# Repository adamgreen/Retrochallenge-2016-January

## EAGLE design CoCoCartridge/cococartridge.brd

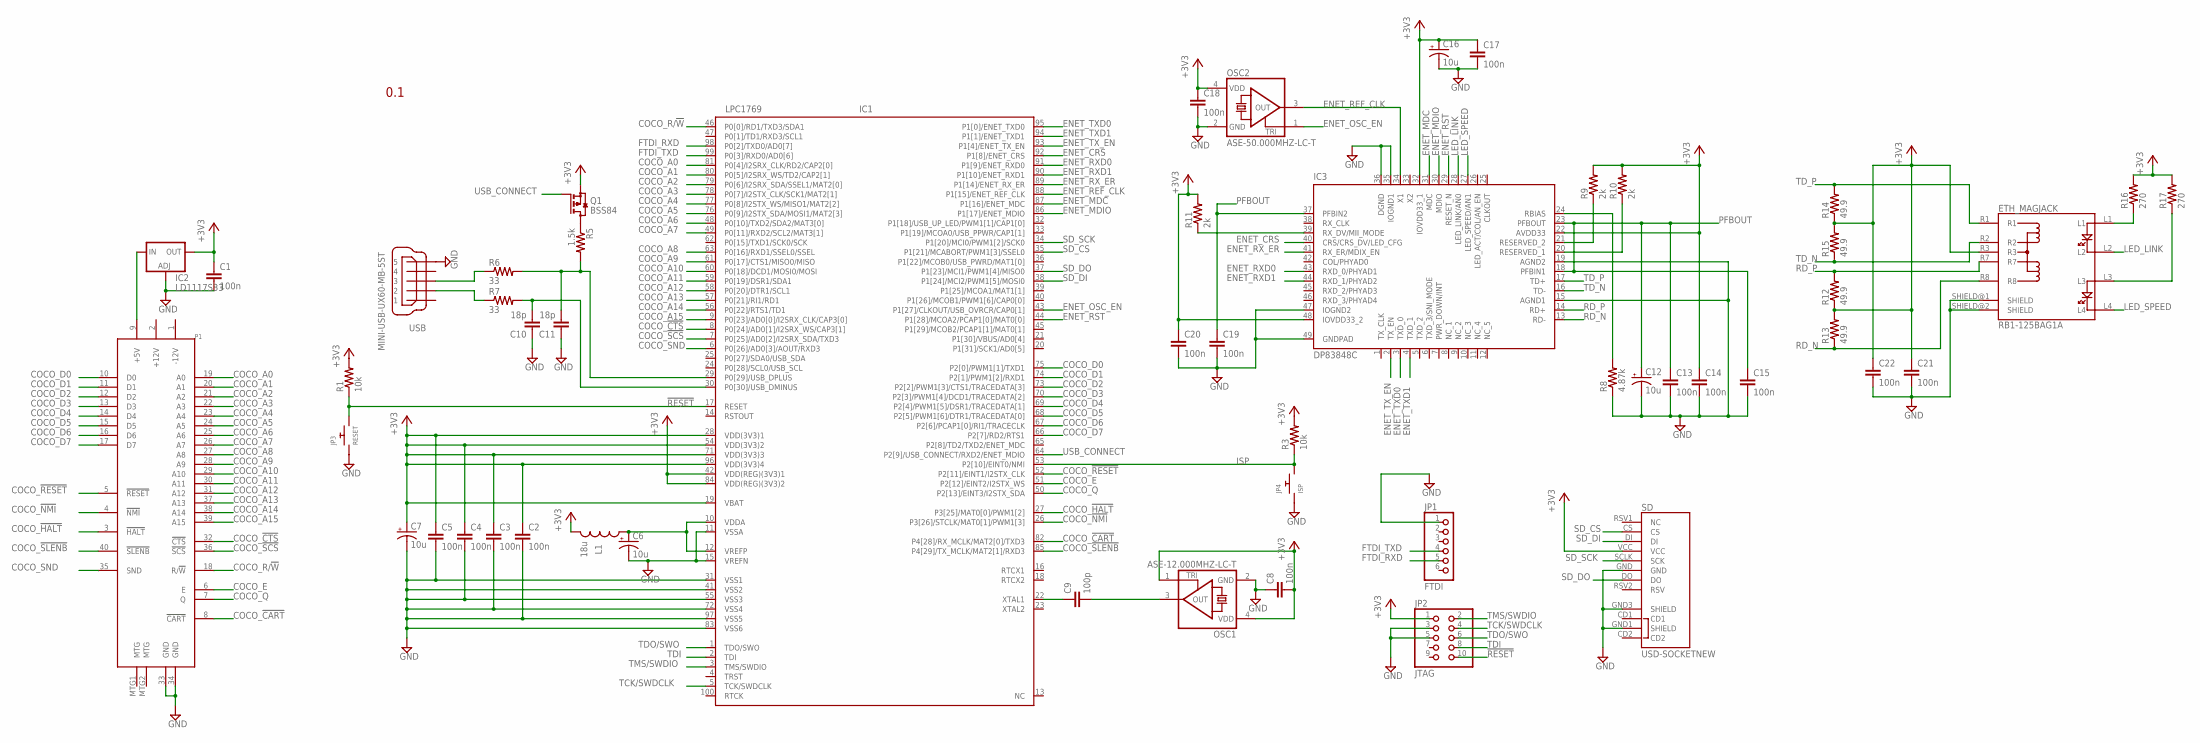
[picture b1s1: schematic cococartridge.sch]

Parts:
C1, C2, C3, C4, C5, C8, C13, C14, C15, C17, C18, C19, C20, C21, C22: 100n; 0805
C6, C7, C12, C16: 10u; EIA3216
C9: 100p; 0805
C10, C11: 18p; 0805
ETH_MAGJACK: RB1-125BAG1A
IC1: LPC1769; LQFP100-14X14
IC2: LD1117S33; SOT223
IC3: DP83848C; LQFP48
JP1: FTDI; 1X06
JP2: JTAG; FTSH-105
JP3: RESET; 1206
JP4: ISP; 1206
L1: 18u; 1210
OSC1: ASE-12.000MHZ-LC-T; ASE
OSC2: ASE-50.000MHZ-LC-T; ASE
P1: COCO-CART3.5X2.5; COCO-CART-3.5X2.5
Q1: BSS84; SOT23
R1, R3: 10k; 0805
R5: 1.5k; 0805
R6, R7: 33; 0805
R8: 4.87k; 0805
R9, R10, R11: 2k; 0805
R12, R13, R14, R15: 49.9; 0805
R16, R17: 270; 0805
SD: USD-SOCKETNEW; MICRO-SD-SOCKET-PP
USB: MINI-USB-UX60-MB-5ST; UX60-MB-5ST

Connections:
!RESET: IC1.17 (RESET), JP2.10, JP3.2, R1.1
+3V3: C1.1, C2.1, C3.1, C4.1, C5.1, C7.A (+), C8.2, C14.1, C16.A (+), C17.1, C18.1, C20.1, C21.1, C22.1, ETH_MAGJACK.R3, IC1.19 (VBAT), IC1.28 (VDD(3V3)1), IC1.42 (VDD(REG)(3V3)1), IC1.54 (VDD(3V3)2), IC1.71 (VDD(3V3)3), IC1.84 (VDD(REG)(3V3)2), IC1.96 (VDD(3V3)4), IC2.4 (OUT), IC3.22 (AVDD33), IC3.32 (IOVDD33_1), IC3.48 (IOVDD33_2), JP2.1, L1.2, OSC1.1 (TRI), OSC1.4 (VDD), OSC2.4 (VDD), Q1.2 (S), R1.2, R3.2, R9.2, R10.2, R11.2, R12.1, R13.2, R14.1, R15.2, R16.2, R17.2, SD.VCC
+5V: IC2.3 (IN), P1.9 (+5V)
COCO_!CART: IC1.82 (P4[28]/RX_MCLK/MAT2[0]/TXD3), P1.8 (!CART)
COCO_!CTS: IC1.8 (P0[24]/AD0[1]/I2SRX_WS/CAP3[1]), P1.32 (!CTS)
COCO_!HALT: IC1.27 (P3[25]/MAT0[0]/PWM1[2]), P1.3 (!HALT)
COCO_!NMI: IC1.26 (P3[26]/STCLK/MAT0[1]/PWM1[3]), P1.4 (!NMI)
COCO_!RESET: IC1.52 (P2[11]/EINT1/I2STX_CLK), P1.5 (!RESET)
COCO_!SCS: IC1.7 (P0[25]/AD0[2]/I2SRX_SDA/TXD3), P1.36 (!SCS)
COCO_!SLENB: IC1.85 (P4[29]/TX_MCLK/MAT2[1]/RXD3), P1.40 (!SLENB)
COCO_A0: IC1.81 (P0[4]/I2SRX_CLK/RD2/CAP2[0]), P1.19 (A0)
COCO_A1: IC1.80 (P0[5]/I2SRX_WS/TD2/CAP2[1]), P1.20 (A1)
COCO_A2: IC1.79 (P0[6]/I2SRX_SDA/SSEL1/MAT2[0]), P1.21 (A2)
COCO_A3: IC1.78 (P0[7]/I2STX_CLK/SCK1/MAT2[1]), P1.22 (A3)
COCO_A4: IC1.77 (P0[8]/I2STX_WS/MISO1/MAT2[2]), P1.23 (A4)
COCO_A5: IC1.76 (P0[9]/I2STX_SDA/MOSI1/MAT2[3]), P1.24 (A5)
COCO_A6: IC1.48 (P0[10]/TXD2/SDA2/MAT3[0]), P1.25 (A6)
COCO_A7: IC1.49 (P0[11]/RXD2/SCL2/MAT3[1]), P1.26 (A7)
COCO_A8: IC1.63 (P0[16]/RXD1/SSEL0/SSEL), P1.27 (A8)
COCO_A9: IC1.61 (P0[17]/CTS1/MISO0/MISO), P1.28 (A9)
COCO_A10: IC1.60 (P0[18]/DCD1/MOSI0/MOSI), P1.29 (A10)
COCO_A11: IC1.59 (P0[19]/DSR1/SDA1), P1.30 (A11)
COCO_A12: IC1.58 (P0[20]/DTR1/SCL1), P1.31 (A12)
COCO_A13: IC1.57 (P0[21]/RI1/RD1), P1.37 (A13)
COCO_A14: IC1.56 (P0[22]/RTS1/TD1), P1.38 (A14)
COCO_A15: IC1.9 (P0[23]/AD0[0]/I2SRX_CLK/CAP3[0]), P1.39 (A15)
COCO_D0: IC1.75 (P2[0]/PWM1[1]/TXD1), P1.10 (D0)
COCO_D1: IC1.74 (P2[1]/PWM1[2]/RXD1), P1.11 (D1)
COCO_D2: IC1.73 (P2[2]/PWM1[3]/CTS1/TRACEDATA[3]), P1.12 (D2)
COCO_D3: IC1.70 (P2[3]/PWM1[4]/DCD1/TRACEDATA[2]), P1.13 (D3)
COCO_D4: IC1.69 (P2[4]/PWM1[5]/DSR1/TRACEDATA[1]), P1.14 (D4)
COCO_D5: IC1.68 (P2[5]/PWM1[6]/DTR1/TRACEDATA[0]), P1.15 (D5)
COCO_D6: IC1.67 (P2[6]/PCAP1[0]/RI1/TRACECLK), P1.16 (D6)
COCO_D7: IC1.66 (P2[7]/RD2/RTS1), P1.17 (D7)
COCO_E: IC1.51 (P2[12]/EINT2/I2STX_WS), P1.6 (E)
COCO_Q: IC1.50 (P2[13]/EINT3/I2STX_SDA), P1.7 (Q)
COCO_R/!W: IC1.46 (P0[0]/RD1/TXD3/SDA1), P1.18 (R/!W)
COCO_SND: IC1.6 (P0[26]/AD0[3]/AOUT/RXD3), P1.35 (SND)
ENET_CRS: IC1.92 (P1[8]/ENET_CRS), IC3.40 (CRS/CRS_DV/LED_CFG)
ENET_MDC: IC1.87 (P1[16]/ENET_MDC), IC3.31 (MDC)
ENET_MDIO: IC1.86 (P1[17]/ENET_MDIO), IC3.30 (MDIO)
ENET_OSC_EN: IC1.43 (P1[27]/CLKOUT/USB_OVRCR/CAP0[1]), OSC2.1 (TRI)
ENET_REF_CLK: IC1.88 (P1[15]/ENET_REF_CLK), IC3.34 (X1), OSC2.3 (OUT)
ENET_RST: IC1.44 (P1[28]/MCOA2/PCAP1[0]/MAT0[0]), IC3.29 (RESET_N)
ENET_RXD0: IC1.91 (P1[9]/ENET_RXD0), IC3.43 (RXD_0/PHYAD1)
ENET_RXD1: IC1.90 (P1[10]/ENET_RXD1), IC3.44 (RXD_1/PHYAD2)
ENET_RX_ER: IC1.89 (P1[14]/ENET_RX_ER), IC3.41 (RX_ER/MDIX_EN)
ENET_TXD0: IC1.95 (P1[0]/ENET_TXD0), IC3.3 (TXD_0)
ENET_TXD1: IC1.94 (P1[1]/ENET_TXD1), IC3.4 (TXD_1)
ENET_TX_EN: IC1.93 (P1[4]/ENET_TX_EN), IC3.2 (TX_EN)
FTDI_RXD: IC1.98 (P0[2]/TXD0/AD0[7]), JP1.5
FTDI_TXD: IC1.99 (P0[3]/RXD0/AD0[6]), JP1.4
GND: C1.2, C2.2, C3.2, C4.2, C5.2, C6.C (-), C7.C (-), C8.1, C10.1, C11.1, C12.C (-), C13.2, C14.2, C15.2, C16.C (-), C17.2, C18.2, C19.2, C20.2, C21.2, C22.2, ETH_MAGJACK.SHIELD@1 (SHIELD), ETH_MAGJACK.SHIELD@2 (SHIELD), IC1.11 (VSSA), IC1.15 (VREFN), IC1.31 (VSS1), IC1.41 (VSS2), IC1.55 (VSS3), IC1.72 (VSS4), IC1.83 (VSS6), IC1.97 (VSS5), IC2.1 (ADJ), IC3.15 (AGND1), IC3.19 (AGND2), IC3.35 (IOGND1), IC3.36 (DGND), IC3.47 (IOGND2), IC3.49 (GNDPAD), JP1.1, JP2.3, JP2.5, JP3.1, JP4.1, OSC1.2 (GND), OSC2.2 (GND), P1.33 (GND), P1.34 (GND), R8.1, SD.GND, SD.GND1 (SHIELD), SD.GND3 (SHIELD), USB.5
ISP: IC1.53 (P2[10]/EINT0/NMI), JP4.2, R3.1
LED_LINK: ETH_MAGJACK.L2, IC3.28 (LED_LINK/AN0)
LED_SPEED: ETH_MAGJACK.L4, IC3.27 (LED_SPEED/AN1)
unnamed: C6.A (+), IC1.10 (VDDA), IC1.12 (VREFP), L1.1
unnamed: C9.1, IC1.22 (XTAL1)
unnamed: C9.2, OSC1.3 (OUT)
unnamed: IC3.24 (RBIAS), R8.2
unnamed: Q1.3 (D), R5.1
unnamed: IC3.39 (RX_DV/MII_MODE), R11.1
unnamed: IC3.21 (RESERVED_2), R9.1
unnamed: IC3.20 (RESERVED_1), R10.1
unnamed: ETH_MAGJACK.L1, R16.1
unnamed: ETH_MAGJACK.L3, R17.1
PFBOUT: C12.A (+), C13.1, C15.1, C19.1, IC3.18 (PFBIN1), IC3.23 (PFBOUT), IC3.37 (PFBIN2)
RD_N: ETH_MAGJACK.R8, IC3.13 (RD-), R13.1
RD_P: ETH_MAGJACK.R7, IC3.14 (RD+), R12.2
SD_CS: IC1.35 (P1[21]/MCABORT/PWM1[3]/SSEL0), SD.CS
SD_DI: IC1.38 (P1[24]/MCI2/PWM1[5]/MOSI0), SD.DI
SD_DO: IC1.37 (P1[23]/MCI1/PWM1[4]/MISO0), SD.DO
SD_SCK: IC1.34 (P1[20]/MCI0/PWM1[2]/SCK0), SD.SCLK (SCK)
TCK/SWDCLK: IC1.5 (TCK/SWDCLK), JP2.4
TDI: IC1.2 (TDI), JP2.8
TDO/SWO: IC1.1 (TDO/SWO), JP2.6
TD_N: ETH_MAGJACK.R2, IC3.16 (TD-), R15.1
TD_P: ETH_MAGJACK.R1, IC3.17 (TD+), R14.2
TMS/SWDIO: IC1.3 (TMS/SWDIO), JP2.2
USB2_N: R7.1, USB.2
USB2_P: R6.1, USB.3
USB_CONNECT: IC1.64 (P2[9]/USB_CONNECT/RXD2/ENET_MDIO), Q1.1 (G)
USB_N: C10.2, IC1.30 (P0[30]/USB_DMINUS), R7.2
USB_P: C11.2, IC1.29 (P0[29]/USB_DPLUS), R5.2, R6.2

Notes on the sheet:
0.1

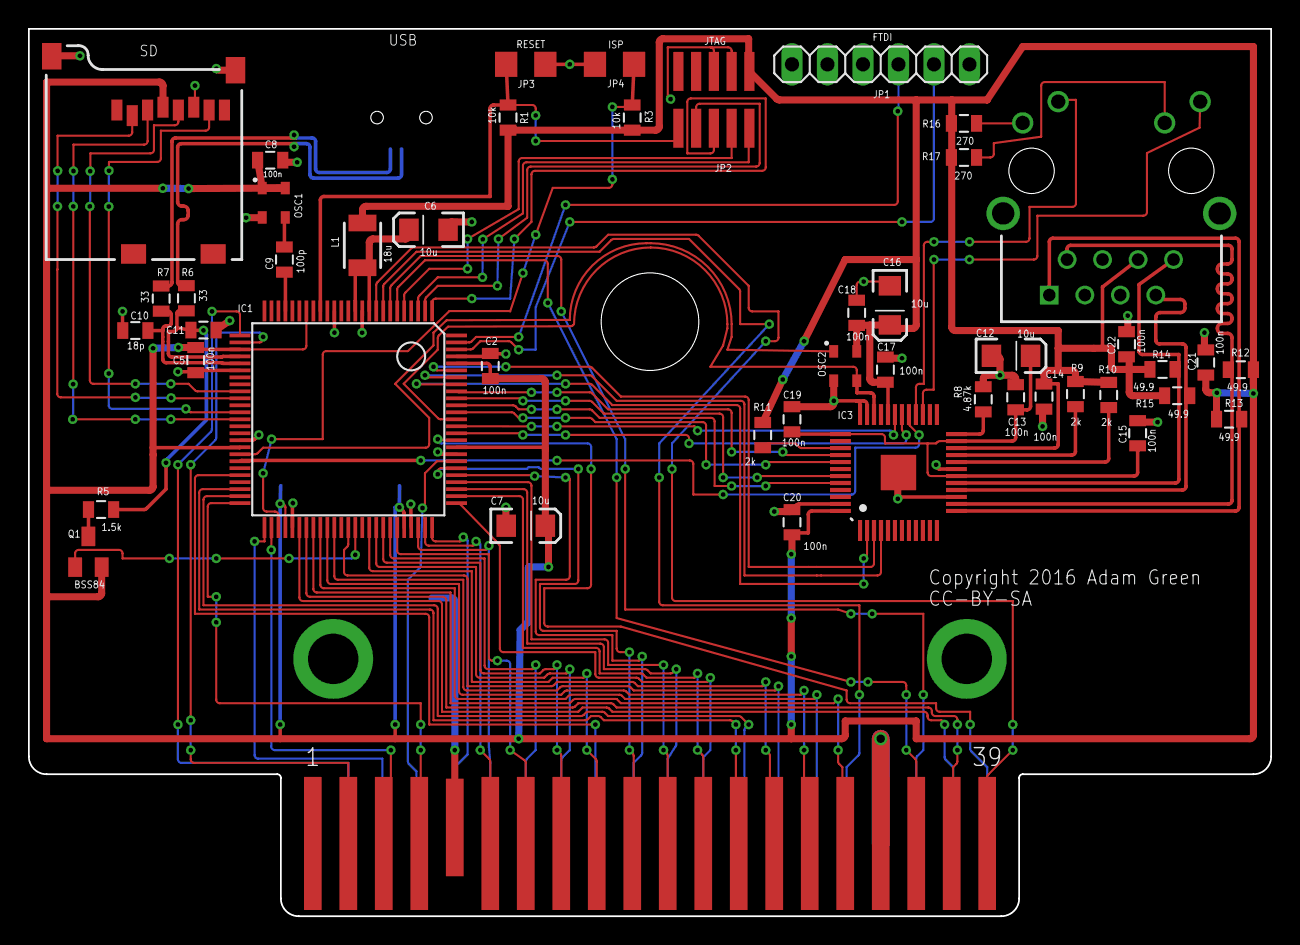
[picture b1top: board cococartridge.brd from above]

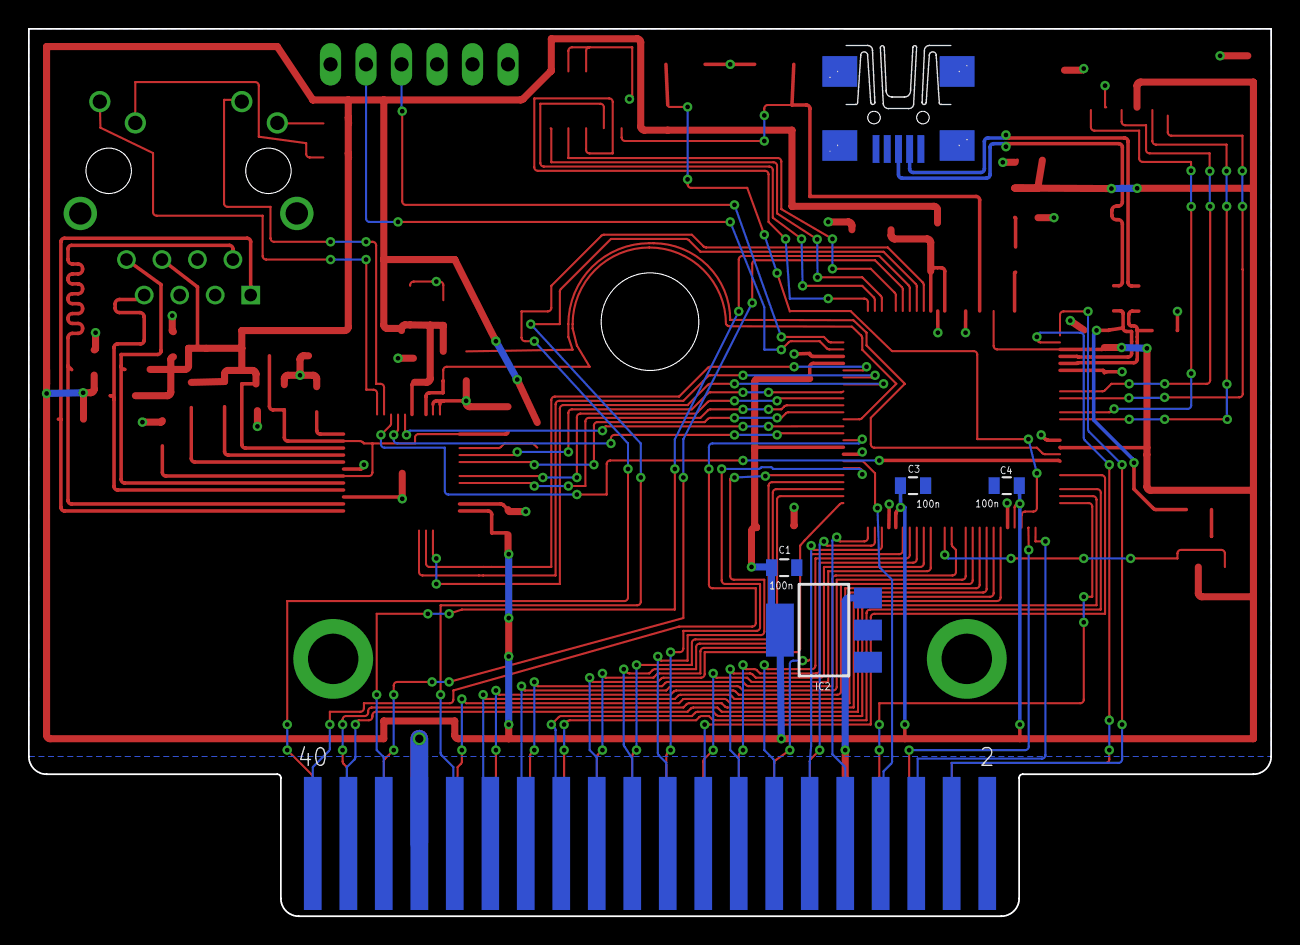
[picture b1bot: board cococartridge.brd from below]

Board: 2 copper layers, 88.9 x 63.5 mm, 52 parts (5 on the bottom side), 84 nets.

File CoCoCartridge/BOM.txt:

Partlist exported from /Users/adamgreen/Documents/eagle/projects/CoCoCartridge/cococartridge.sch at 1/11/16 1:07 AM

Qty Value                Device               Package            Parts                                                               Description
1   1.5k                 RESISTOR0805-RES     0805               R5                                                                  Resistor
15  100n                 CAP0805              0805               C1, C2, C3, C4, C5, C8, C13, C14, C15, C17, C18, C19, C20, C21, C22 Capacitor
1   100p                 CAP0805              0805               C9                                                                  Capacitor
2   10k                  RESISTOR0805-RES     0805               R1, R3                                                              Resistor
4   10u                  CAP_POL1206          EIA3216            C6, C7, C12, C16                                                    Capacitor Polarized
2   18p                  CAP0805              0805               C10, C11                                                            Capacitor
1   18u                  INDUCTOR1210         1210               L1                                                                  Inductors
2   270                  RESISTOR0805-RES     0805               R16, R17                                                            Resistor
3   2k                   RESISTOR0805-RES     0805               R9, R10, R11                                                        Resistor
2   33                   RESISTOR0805-RES     0805               R6, R7                                                              Resistor
1   4.87k                RESISTOR0805-RES     0805               R8                                                                  Resistor
4   49.9                 RESISTOR0805-RES     0805               R12, R13, R14, R15                                                  Resistor
1   ASE-12.000MHZ-LC-T   ASE                  ASE                U$1                                                                 3.3Vdc CMOS SMD CRYSTAL CLOCK OSCILLATOR
1   ASE-50.000MHZ-LC-T   ASE                  ASE                U$2                                                                 3.3Vdc CMOS SMD CRYSTAL CLOCK OSCILLATOR
1   BSS84                BSS84                SOT23              Q1                                                                  P-CHANNEL MOS FET
1   COCO-CART            COCO-CART            COCO-CART-2.1X1.75 P1                                                                  Tandy/TRS-80 Color Computer Cartridge Connector
1   DP83848C             DP83848C             LQFP48             IC3                                                                 PHYTER® - Extended Temperature Single Port 10/100 Mb/s Ethernet Physical Layer Transceiver
1   FTDI                 PINHD-1X6            1X06               JP1                                                                 PIN HEADER
1   JTAG                 FTSH-105             FTSH-105           JP2                                                                 Semtec FSH-105 2x5 SMT Micro Header
2   JUMPER-1206          JUMPER-1206          1206               JP3, JP4                                                            Jumper based on 1206 SMT pads
1   LD1117S33            LD117AS33TR          SOT223             IC2                                                                 Low drop fixed and adjustable positive voltage regulators 1 A
1   LPC1769              LPC1769              LQFP100-14X14      IC1                                                                 LPC1769 120 MHz 32-bit ARM Cortex-M3 based microcontroller featuring a high level of integration and low power consumption. 512 kB Flash, 64 kB SRAM, USB Device/Host/OTG, 2 CAN, DAC, Ethernet MarcVl - Datasheet available on www.nxp.com
1   MINI-USB-UX60-MB-5ST MINI-USB-UX60-MB-5ST UX60-MB-5ST        X1                                                                  MINI USB Connector
1   RB1-125BAG1A         RB1-125BAG1A         RB1-125BAG1A       ETH_MAGJACK                                                         MagJack RB1-125BAG1A
1   USD-SOCKETNEW        USD-SOCKETNEW        MICRO-SD-SOCKET-PP U1                                                                  microSD Socket

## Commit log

2015-12-10 Update Dec 10th notes
2015-12-10 Ignore .DS_Store
2015-12-14 Fix typos
2016-01-08 January 8th notes
2016-01-12 Initial commit of CoCoCartridge Eagle project
    The Eagle project only contains my first attempt at the schematic so
    far. It interfaces a NXP LPC1769 Cortex-M3 microcontroller to the
    CoCo cartridge port. The LPC1768 takes advantage of its USB and
    Ethernet peripheral blocks to communicate with modern hardware and
    uses SPI to provide access to uSD cards.
    Uses the following license:
2016-01-13 Add scaled down image of schematic
    This is just a thumbnail of the actual schematic PDF.
2016-01-13 January 13th notes
2016-01-22 Add recent project photos
2016-01-22 January 21st notes
2016-01-30 First attempt at manual routing
    Yet to be done:
    * Get it reviewed by an actual EE.
    * Clean up the component labels, etc.
    * Verify component footprints.
2016-01-31 Add photo of board
    This is a screen capture of the board after I first got all of the
    traces placed.
2016-01-31 January 30th notes
2016-02-01 Add copyright text to board silkscreen
    CC-BY-SA
2016-02-01 February 1st notes
2016-02-06 Add attribution for Mark J. Blair's previous work
2016-02-09 Revision 1.0 sent to OSHPark
    This is the first version that I sent off to OSHPark for manufacturing
    tonight.
2016-03-25 Fix missing Gnd connection on SD socket
    I connected the shield pins labelled ground to the actual ground but
    forgot to connect the actual ground pin of the SD card to my ground
    plane.

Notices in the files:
CoCoCartridge/cococartridge.brd:
Copyright 2016 Adam Green
CC-BY-SA
parts and their libraries:
SparkFun-Passives: Licensing: Creative Commons ShareAlike 4.0 International - https://creativecommons.org/licenses/by-sa/4.0
adam_custom: Released under the Creative Commons
adam_custom: https://creativecommons.org/licenses/by-sa/4.0
